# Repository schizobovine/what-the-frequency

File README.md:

What's the Frequency, Arduino?
==================

What The Frequency is an Arduino-compatible frequency counter with a 4040N to extend the measurement range. Based on the [SparkFun]() [Frequency Counter Kit](https://www.sparkfun.com/products/10140), which in turn is based on [FunCount](http://www.nuxie1.com/guides/funcount-frequency-counter.html) by Nuxie.

My original goal was to understand how/why the ground shunt capacitors are necessary when one includes a crystal oscillator as a clock for a microcontroller. I wanted to see if the calculations I was making based on load capacitance had any bearing at all on the circuit, and by how much.

Three herds of bald yaks later, this almost-but-not-quite circuit is what I have. So it goes.

My modifications include:
* 4040 12-bit binary ripple counter to extend the measurable range beyond 8MHz
* Shrink the LCD down a bit
* Size the PCB to fit a [Hammond 1591XXA enclosure](http://www.hammondmfg.com/dwg2XX.htm)
* DC barrel jack and voltage regulator
* Some kind of external probe (this was a terrible idea)

In the process, I've leared more than a bit about how oscillators work, PCB design, and just how little my CS education prepared me for electrical engineering. ;)

As it stands, the project is incomplete: in my haste to get a damn board back
from OSHPark, I didn't thoroughly think through the design. There's a single
external probe connection...and no ground. And that adding those would upset
the measurement by adding a ton of extra capacitance, enough to swamp the
difference between a 22pF and a 30pF cap.

So, in the interest of building something useable but still having a modicum of
accuracy, I'm going to be including another Atmel chip (likely the ATTiny84,
since the 85 has the clock output on the same pin as the input for running a
crystal osciallator circuit) to get a given crystal circuit oscillating. By
calibrating and measuring the capacitance (and then accounting for that), I
should be have a test harness for the typical Pierce oscillator setup that
seems to get used a lot.

Licensed under the same Creative Commons BY-NC-SA 3.0 license as the kit I was
basing it on (though it's pretty much completely diverged at this point). I've been using CC-BY-SA-4.0 since I don't give a crap if you make money off this or not. Honestly, if you're using my board designs and selling them to people,
1. You're an idiot
2. You're gonna get sued when someone catches on fire (probably an orphanage)
3. I DISCLAIM ALL LIABILITY FOR THE USE OF THIS. USE AT YOUR OWN RISK.

YMMV, check with your doctor before taking Frequenizole, etc.

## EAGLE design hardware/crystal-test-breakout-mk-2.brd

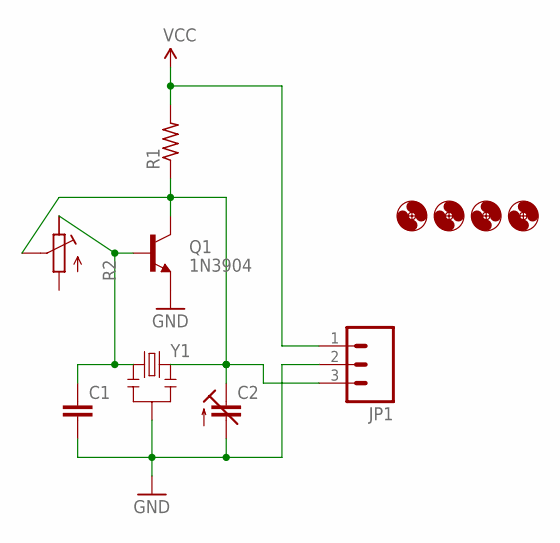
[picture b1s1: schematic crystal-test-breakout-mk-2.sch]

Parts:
C1: CAPACITOR-CERAMIC025-025X050; C025-025X050
C2: CAPACITOR-TRIM3040.427; CTRIM3040.427
H1, H2, H3, H4: HOLE#2; HOLE-#2
JP1: M03PTH; 1X03
Q1: 1N3904; TO-92-AMMO
R1: RESISTORPTH-AXIAL-5.08MM; RESISTOR-AXIAL-PTH-5.08MM
R2: POTENTIOMETER3296W; RTRIM3296W
Y1: RESONATORPTH-BIGHOLES; RESONATOR-PTH-BIGHOLES

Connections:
GND: C1.2, C2.2 (A), JP1.2, Q1.1 (E), Y1.2
unnamed: C1.1, Q1.2 (B), R2.3 (E), Y1.1
unnamed: C2.1A (E), C2.1B (E), JP1.3, Q1.3 (C), R1.P$1 (1), R2.2 (S), Y1.3
VCC: JP1.1, R1.P$2 (2)

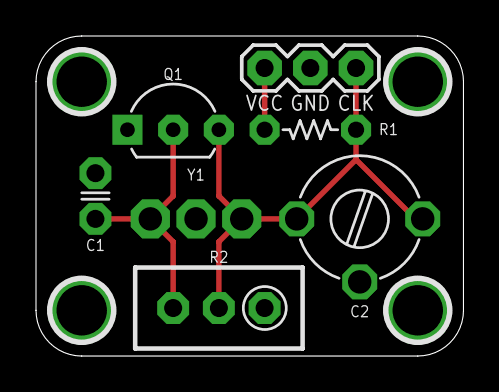
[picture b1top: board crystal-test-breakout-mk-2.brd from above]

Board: 2 copper layers, 23.7 x 17.8 mm, 12 parts (1 on the bottom side), 4 nets.

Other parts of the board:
U$1: CC-BY-SA-4.0-NO-URL

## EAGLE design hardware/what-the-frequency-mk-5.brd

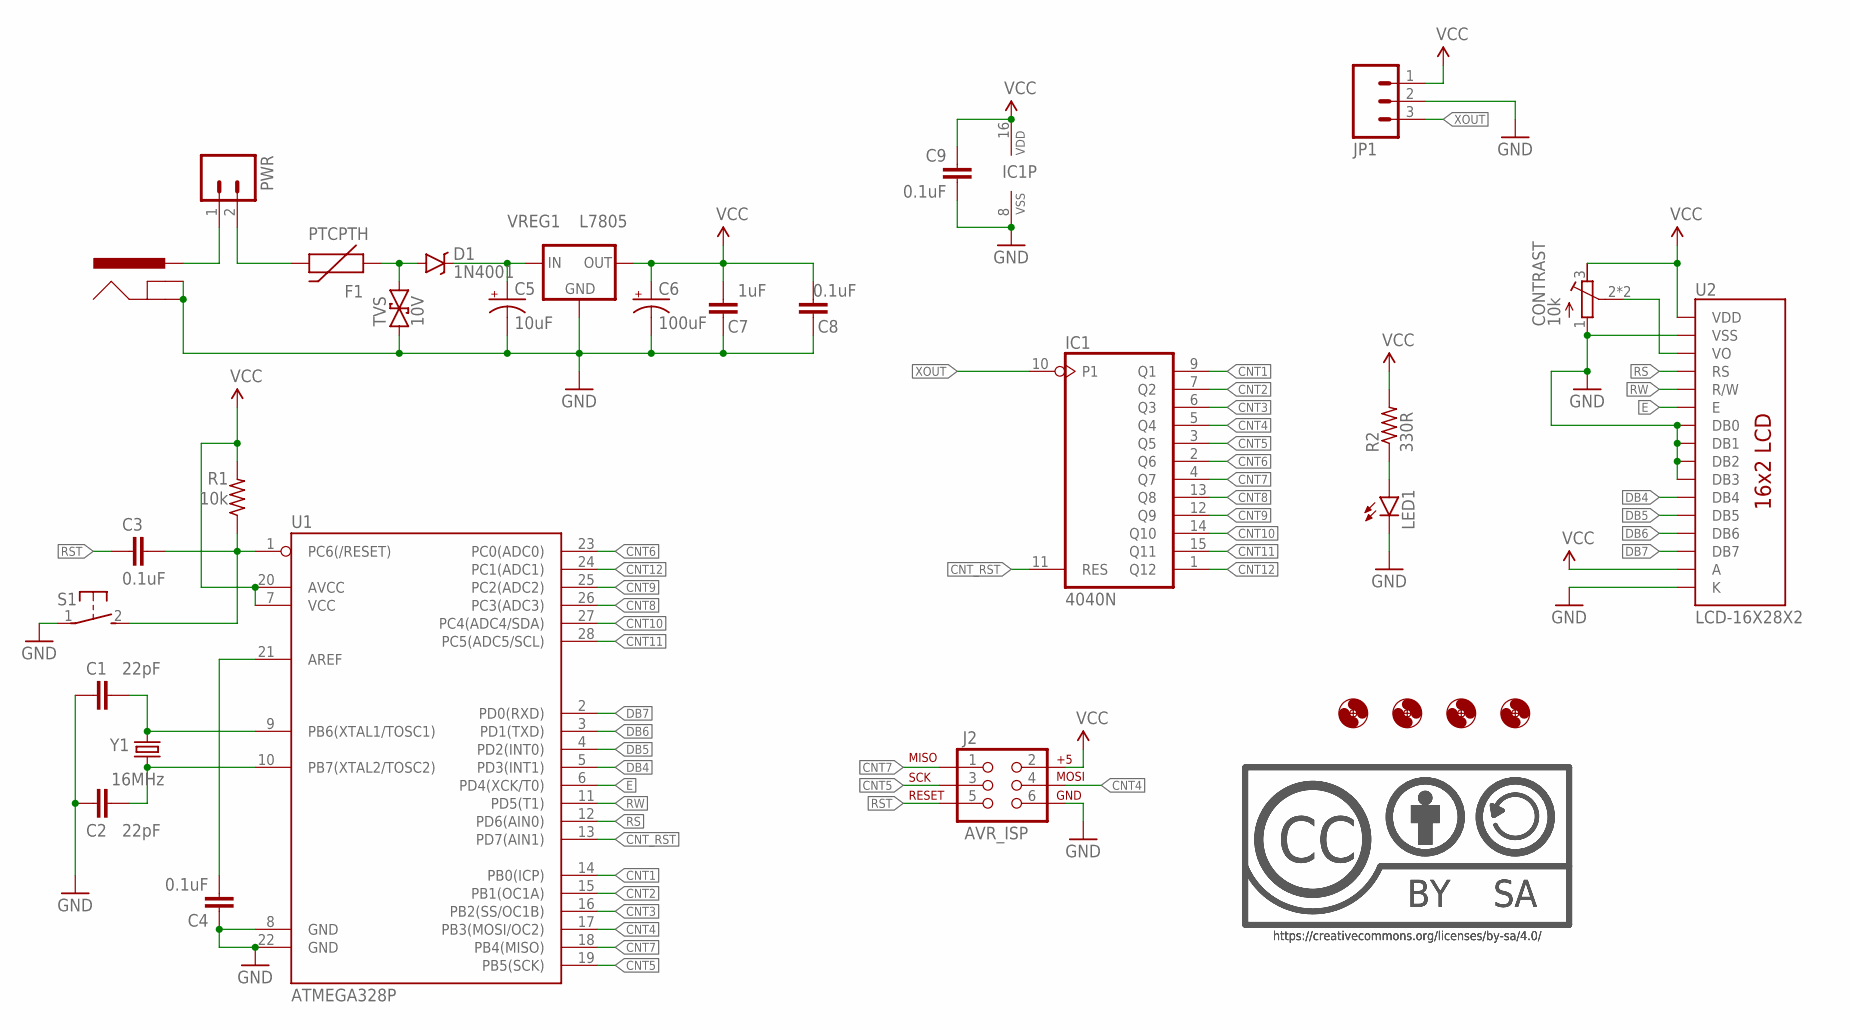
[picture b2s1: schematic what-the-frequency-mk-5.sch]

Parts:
C1, C2: 22pF; C025-024X044
C3, C4, C8, C9: 0.1uF; C025-024X044
C5: 10uF; E2-5
C6: 100uF; E2,5-6
C7: 1uF; C025-024X044
CONTRAST: 10k; POT-THUMBWHEEL
D1: 1N4001; DO-41
F1: PTCPTH; PTC
H1, H2, H3, H4: HOLE#4; HOLE-#4
IC1: 4040N; DIL16
J1: POWER_JACKPTH; POWER_JACK_PTH
J2: AVR_ISP; AVR_MINI_PROG
JP1: M03PTH; 1X03
LED1: LED3MM
PWR: M02PTH; 1X02
R1: 10k; RESISTOR-AXIAL-PTH-7.68MM
R2: 330R; RESISTOR-AXIAL-PTH-6.35MM
S1: DTS-3
TVS: 10V; DO-41-TVS
U1: ATMEGA328P; DIL28-3
U2: LCD-16X28X2; LCD-8X2
U$3, U$7: CC-BY-SA-4.0NO-URL; CC-BY-SA-4.0-NO-URL
VREG1: L7805; TO220V
Y1: 16MHz; HC49U-V

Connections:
CNT1: IC1.9 (Q1), U1.14 (PB0(ICP))
CNT2: IC1.7 (Q2), U1.15 (PB1(OC1A))
CNT3: IC1.6 (Q3), U1.16 (PB2(SS/OC1B))
CNT4: IC1.5 (Q4), J2.4, U1.17 (PB3(MOSI/OC2))
CNT5: IC1.3 (Q5), J2.3, U1.19 (PB5(SCK))
CNT6: IC1.2 (Q6), U1.23 (PC0(ADC0))
CNT7: IC1.4 (Q7), J2.1, U1.18 (PB4(MISO))
CNT8: IC1.13 (Q8), U1.26 (PC3(ADC3))
CNT9: IC1.12 (Q9), U1.25 (PC2(ADC2))
CNT10: IC1.14 (Q10), U1.27 (PC4(ADC4/SDA))
CNT11: IC1.15 (Q11), U1.28 (PC5(ADC5/SCL))
CNT12: IC1.1 (Q12), U1.24 (PC1(ADC1))
CNT_RST: IC1.11 (RES), U1.13 (PD7(AIN1))
DB4: U1.5 (PD3(INT1)), U2.11 (DB4)
DB5: U1.4 (PD2(INT0)), U2.12 (DB5)
DB6: U1.3 (PD1(TXD)), U2.13 (DB6)
DB7: U1.2 (PD0(RXD)), U2.14 (DB7)
E: U1.6 (PD4(XCK/T0)), U2.6 (E)
GND: C1.2, C2.2, C4.1, C5.-, C6.-, C7.1, C8.1, C9.1, CONTRAST.1 (A), IC1.8 (VSS), J1.GND, J1.GNDBREAK, J2.6, JP1.2, LED1.K (C), S1.1, TVS.P$1 (1), U1.8 (GND), U1.22 (GND), U2.1 (VSS), U2.7 (DB0), U2.8 (DB1), U2.9 (DB2), U2.10 (DB3), U2.16 (K), VREG1.2 (GND)
unnamed: C5.+, D1.C, VREG1.1 (IN)
unnamed: LED1.A, R2.P$1 (1)
unnamed: J1.PWR, PWR.1
unnamed: D1.A, F1.P$1 (1), TVS.P$2 (2)
unnamed: F1.P$2 (2), PWR.2
unnamed: C1.1, U1.9 (PB6(XTAL1/TOSC1)), Y1.2
unnamed: C2.1, U1.10 (PB7(XTAL2/TOSC2)), Y1.1
unnamed: C4.2, U1.21 (AREF)
unnamed: CONTRAST.2 (S), CONTRAST.2@1 (S), U2.3 (VO)
unnamed: C3.2, R1.P$1 (1), S1.2, U1.1 (PC6(/RESET))
RS: U1.12 (PD6(AIN0)), U2.4 (RS)
RST: C3.1, J2.5
RW: U1.11 (PD5(T1)), U2.5 (R/W)
VCC: C6.+, C7.2, C8.2, C9.2, CONTRAST.3 (E), IC1.16 (VDD), J2.2, JP1.1, R1.P$2 (2), R2.P$2 (2), U1.7 (VCC), U1.20 (AVCC), U2.2 (VDD), U2.15 (A), VREG1.3 (OUT)
XOUT: IC1.10 (P1), JP1.3

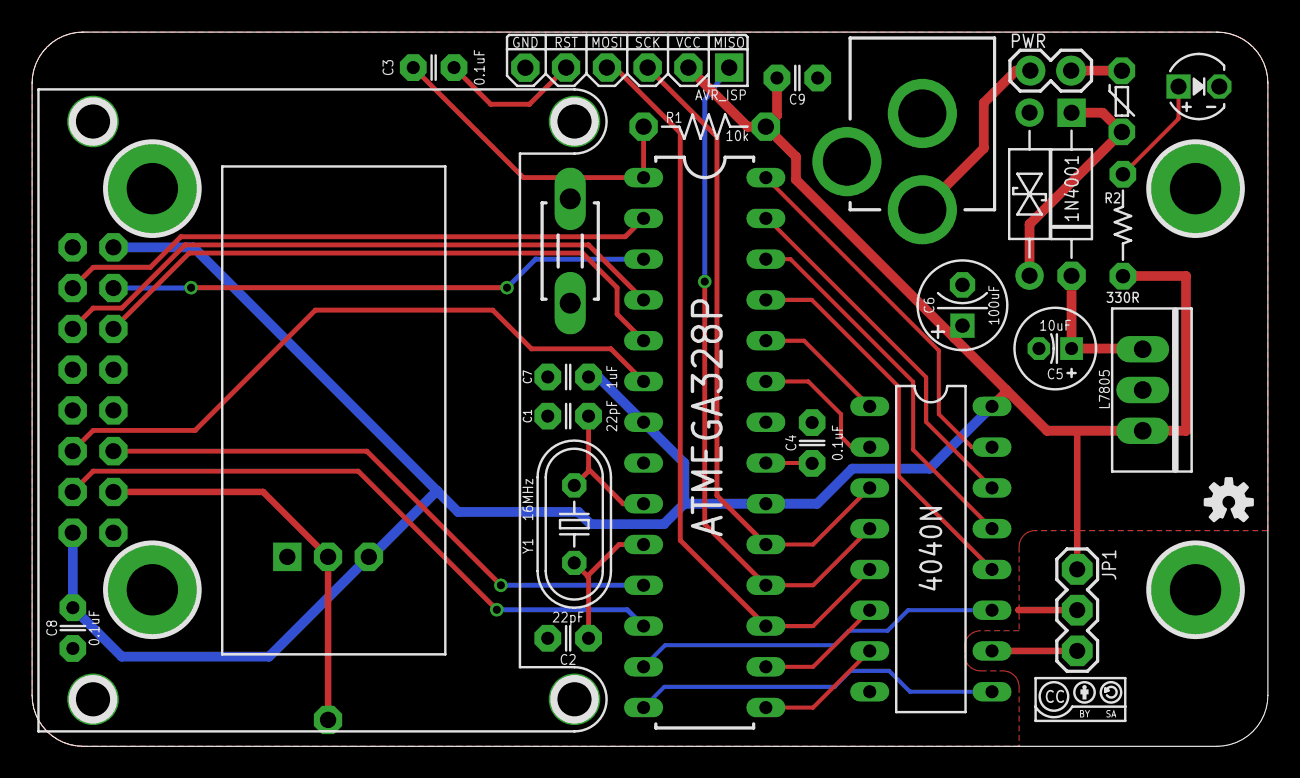
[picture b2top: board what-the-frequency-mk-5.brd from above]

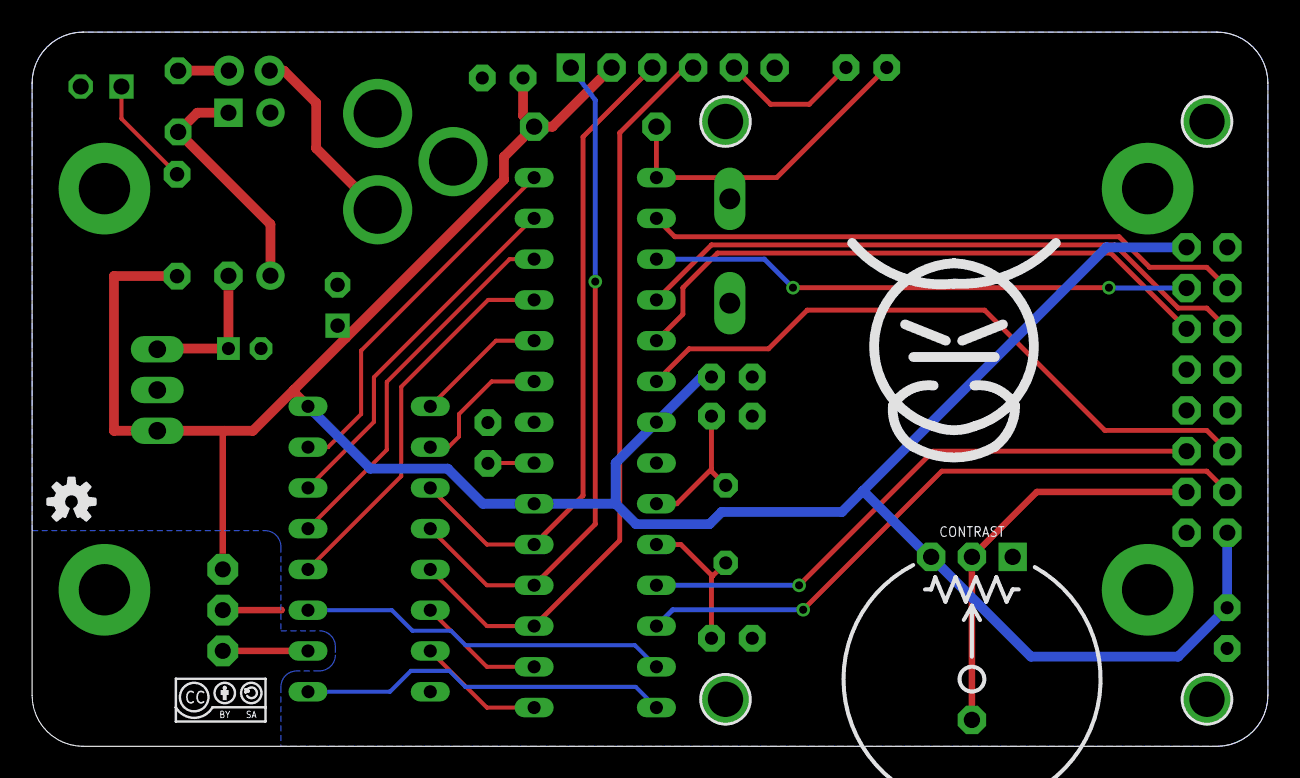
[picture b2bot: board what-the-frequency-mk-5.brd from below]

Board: 2 copper layers, 77.0 x 44.5 mm, 35 parts (4 on the bottom side), 34 nets.

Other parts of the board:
U$2, U$4: OSHW-LOGO-S
U$8: COW

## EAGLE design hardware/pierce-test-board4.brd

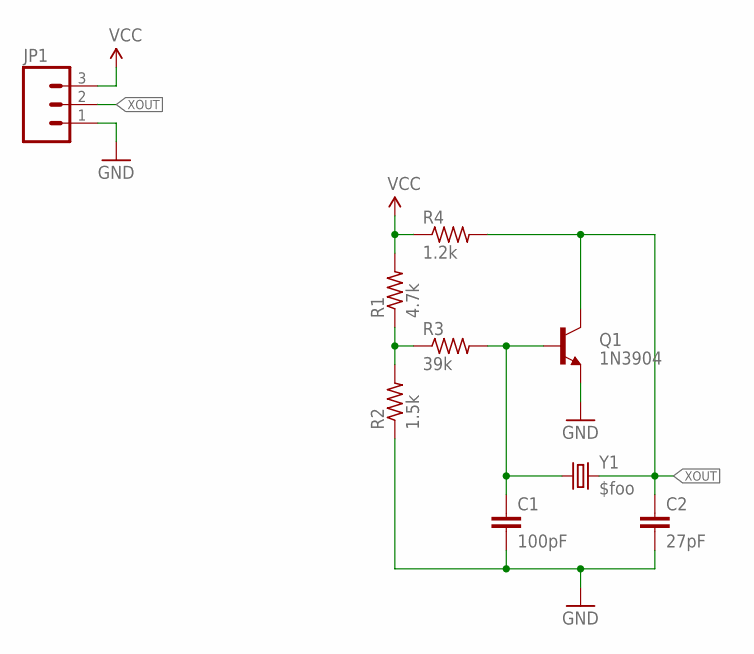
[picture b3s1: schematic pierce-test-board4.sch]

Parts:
C1: 100pF; C025-024X044
C2: 27pF; C025-024X044
JP1: M03PTH; 1X03
Q1: 1N3904; TO-92-AMMO
R1: 4.7k; RESISTOR-AXIAL-PTH-5.08MM
R2: 1.5k; RESISTOR-AXIAL-PTH-5.08MM
R3: 39k; RESISTOR-AXIAL-PTH-5.08MM
R4: 1.2k; RESISTOR-AXIAL-PTH-5.08MM
Y1: $foo; HC49U-V

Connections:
GND: C1.2, C2.2, JP1.1, Q1.1 (E), R2.P$1 (1)
unnamed: R1.P$1 (1), R2.P$2 (2), R3.P$1 (1)
unnamed: C1.1, Q1.2 (B), R3.P$2 (2), Y1.1
VCC: JP1.3, R1.P$2 (2), R4.P$1 (1)
XOUT: C2.1, JP1.2, Q1.3 (C), R4.P$2 (2), Y1.2

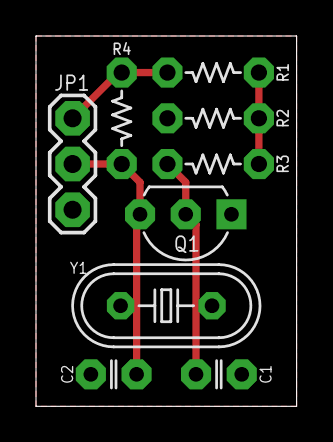
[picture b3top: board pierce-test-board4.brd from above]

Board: 2 copper layers, 14.5 x 20.6 mm, 10 parts (1 on the bottom side), 5 nets.

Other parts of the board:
U$1: CC-BY-SA-4.0-NO-URL

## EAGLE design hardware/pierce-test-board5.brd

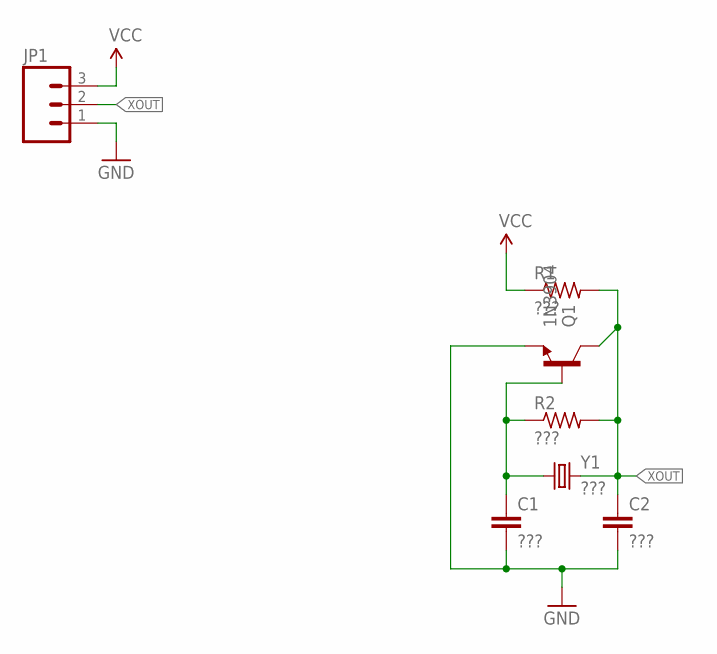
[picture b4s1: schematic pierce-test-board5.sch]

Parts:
C1, C2: ???; C025-024X044
JP1: M03PTH; 1X03
Q1: 1N3904; TO-92-AMMO
R1, R2: ???; RESISTOR-AXIAL-PTH-5.08MM
Y1: ???; HC49U-V

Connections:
GND: C1.2, C2.2, JP1.1, Q1.1 (E)
unnamed: C1.1, Q1.2 (B), R2.P$1 (1), Y1.1
VCC: JP1.3, R1.P$1 (1)
XOUT: C2.1, JP1.2, Q1.3 (C), R1.P$2 (2), R2.P$2 (2), Y1.2

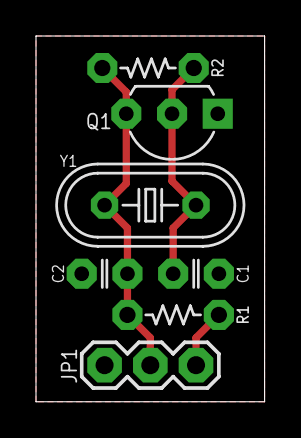
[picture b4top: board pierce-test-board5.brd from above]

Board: 2 copper layers, 12.7 x 20.3 mm, 8 parts (1 on the bottom side), 4 nets.

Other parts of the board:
U$1: CC-BY-SA-4.0-NO-URL

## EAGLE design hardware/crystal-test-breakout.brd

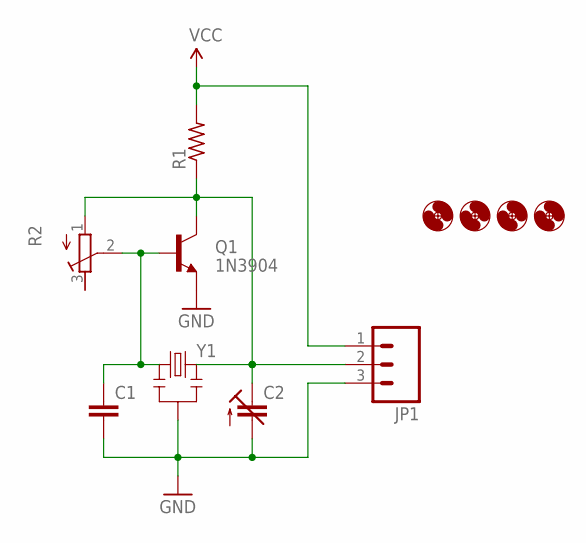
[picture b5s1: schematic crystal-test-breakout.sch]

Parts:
C1: CAPACITOR-CERAMIC025-025X050; C025-025X050
C2: CAPACITOR-TRIMGYC40000; GYC40000
H1, H2, H3, H4: HOLE#2; HOLE-#2
JP1: M03PTH; 1X03
Q1: 1N3904; TO-92-AMMO
R1: RESISTORPTH-AXIAL-5.08MM; RESISTOR-AXIAL-PTH-5.08MM
R2: POTENTIOMETER3296W; RTRIM3296W
Y1: RESONATORPTH; RESONATOR-PTH

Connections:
GND: C1.2, C2.P$1 (A), JP1.3, Q1.1 (E), Y1.2
unnamed: C1.1, Q1.2 (B), R2.2 (S), Y1.1
unnamed: C2.P$2 (E), C2.P$3 (E), JP1.2, Q1.3 (C), R1.P$1 (1), R2.1 (A), Y1.3
VCC: JP1.1, R1.P$2 (2)

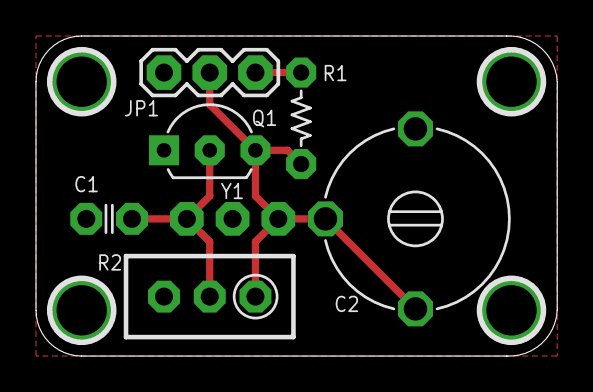
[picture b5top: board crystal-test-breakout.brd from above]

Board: 2 copper layers, 29.0 x 17.8 mm, 11 parts (0 on the bottom side), 4 nets.

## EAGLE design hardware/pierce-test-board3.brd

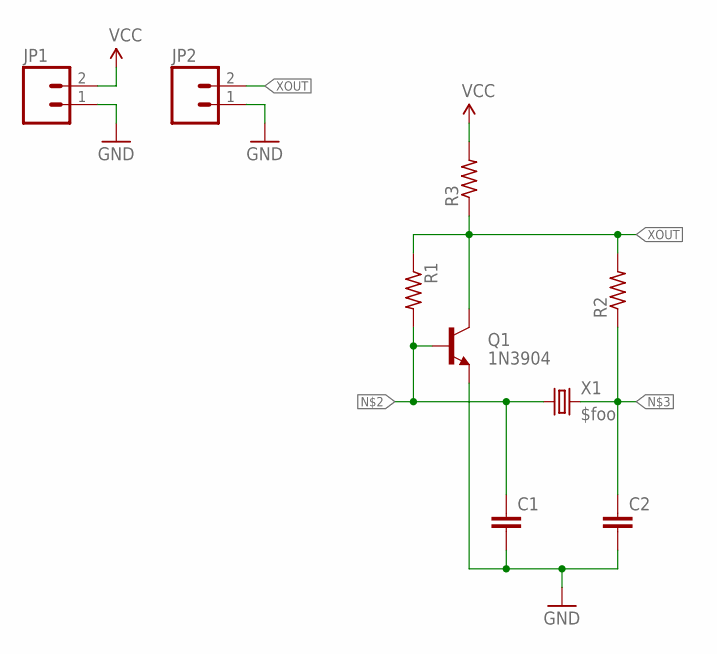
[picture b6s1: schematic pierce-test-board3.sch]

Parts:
C1, C2: CAPACITOR-CERAMIC025-024X044; C025-024X044
JP1, JP2: M02PTH; 1X02
Q1: 1N3904; TO-92-AMMO
R1, R2, R3: RESISTORPTH-AXIAL-5.08MM; RESISTOR-AXIAL-PTH-5.08MM
X1: $foo; HC49U-V

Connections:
GND: C1.2, C2.2, JP1.1, JP2.1, Q1.1 (E)
unnamed: C1.1, Q1.2 (B), R1.P$2 (2), X1.1
unnamed: C2.1, R2.P$1 (1), X1.2
VCC: JP1.2, R3.P$2 (2)
XOUT: JP2.2, Q1.3 (C), R1.P$1 (1), R2.P$2 (2), R3.P$1 (1)

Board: 2 copper layers, 9 parts (0 on the bottom side), 5 nets, no tracks yet.

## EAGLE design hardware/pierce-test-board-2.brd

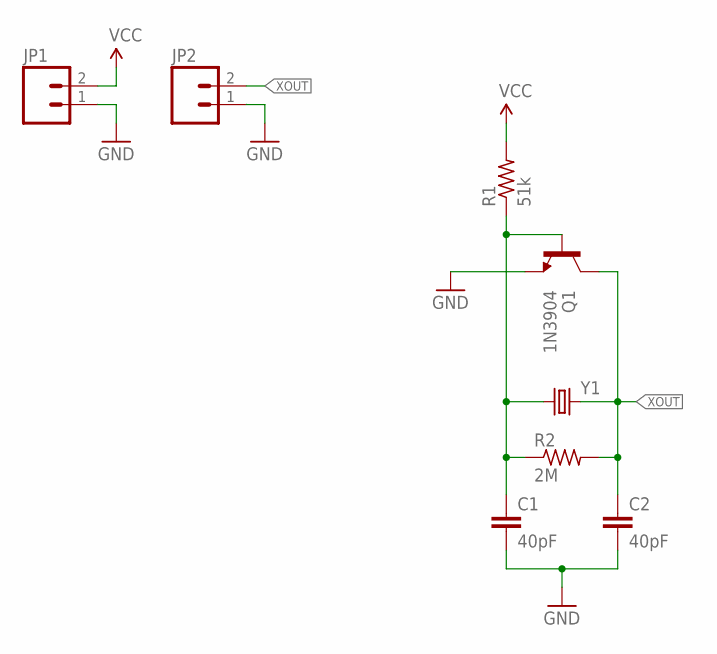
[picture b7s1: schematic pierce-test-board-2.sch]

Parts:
C1, C2: 40pF; C025-024X044
JP1, JP2: M02PTH; 1X02
Q1: 1N3904; TO-92-AMMO
R1: 51k; RESISTOR-AXIAL-PTH-7.68MM
R2: 2M; RESISTOR-AXIAL-PTH-7.68MM
Y1: CRYSTALHC49UV; HC49U-V

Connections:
GND: C1.2, C2.2, JP1.1, JP2.1, Q1.1 (E)
unnamed: C1.1, Q1.2 (B), R1.P$1 (1), R2.P$1 (1), Y1.1
VCC: JP1.2, R1.P$2 (2)
XOUT: C2.1, JP2.2, Q1.3 (C), R2.P$2 (2), Y1.2

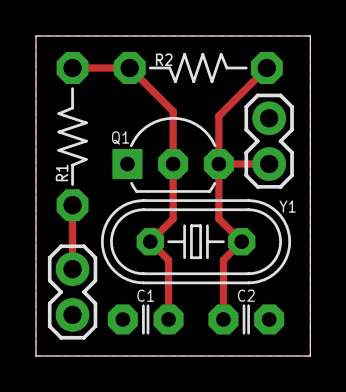
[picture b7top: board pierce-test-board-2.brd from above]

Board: 2 copper layers, 15.2 x 17.8 mm, 9 parts (1 on the bottom side), 4 nets.

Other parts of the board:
U$1: CC-BY-SA-4.0-NO-URL

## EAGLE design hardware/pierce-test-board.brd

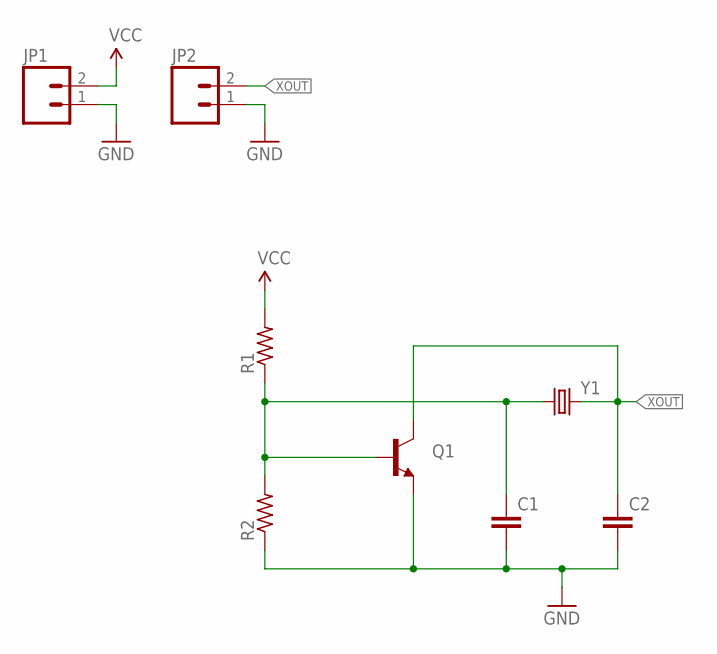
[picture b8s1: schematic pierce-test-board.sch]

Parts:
C1, C2: CAPACITOR-CERAMIC025-024X044; C025-024X044
JP1, JP2: M02PTH; 1X02
Q1: TRANSISTOR_NPNTO-92-AMMO-EBC; TO-92-AMMO
R1, R2: RESISTORPTH-AXIAL-5.08MM; RESISTOR-AXIAL-PTH-5.08MM
Y1: CRYSTALHC49UV; HC49U-V

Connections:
GND: C1.2, C2.2, JP1.1, JP2.1, Q1.1 (E), R2.P$1 (1)
unnamed: C1.1, Q1.2 (B), R1.P$1 (1), R2.P$2 (2), Y1.1
VCC: JP1.2, R1.P$2 (2)
XOUT: C2.1, JP2.2, Q1.3 (C), Y1.2

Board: 2 copper layers, 8 parts (0 on the bottom side), 4 nets, no tracks yet.

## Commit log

2014-09-25 newer revisions of the board, including the first one sent for fabrication
2014-09-25 start of mark 4 board to include clock driving circuit
2014-09-26 test oscillator PCBs
2014-09-26 updating license and readme
2014-09-26 i hate merging
2014-09-26 some more test osc boards
2014-09-29 MOAR BOARDS FOR THE BOARD THRONE
2014-09-29 yet another test pcb
2014-09-29 putting trimpot on its side for less whoopsy-daisy factor
2014-10-08 blah
2014-10-15 new breakout for larger form factor varicap
2014-10-26 klasdjcvkilasdjfl

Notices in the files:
parts and their libraries:
SparkFun-FreqCtrl: Licensing: Creative Commons ShareAlike 4.0 International - https://creativecommons.org/licenses/by-sa/4.0
A_butts: creativecommons.org/licenses/by-sa/4.0
A_butts: https://creativecommons.org/licenses/by-sa/4.0
